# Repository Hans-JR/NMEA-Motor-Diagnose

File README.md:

# NMEA-Motor-Diagnose
Monitors several Boot Engine Parameter and converts them into the NMEA0183 protocoll

The Project is listet under the URL https://open-boat-projects.org/de/diy-motordiagnose/

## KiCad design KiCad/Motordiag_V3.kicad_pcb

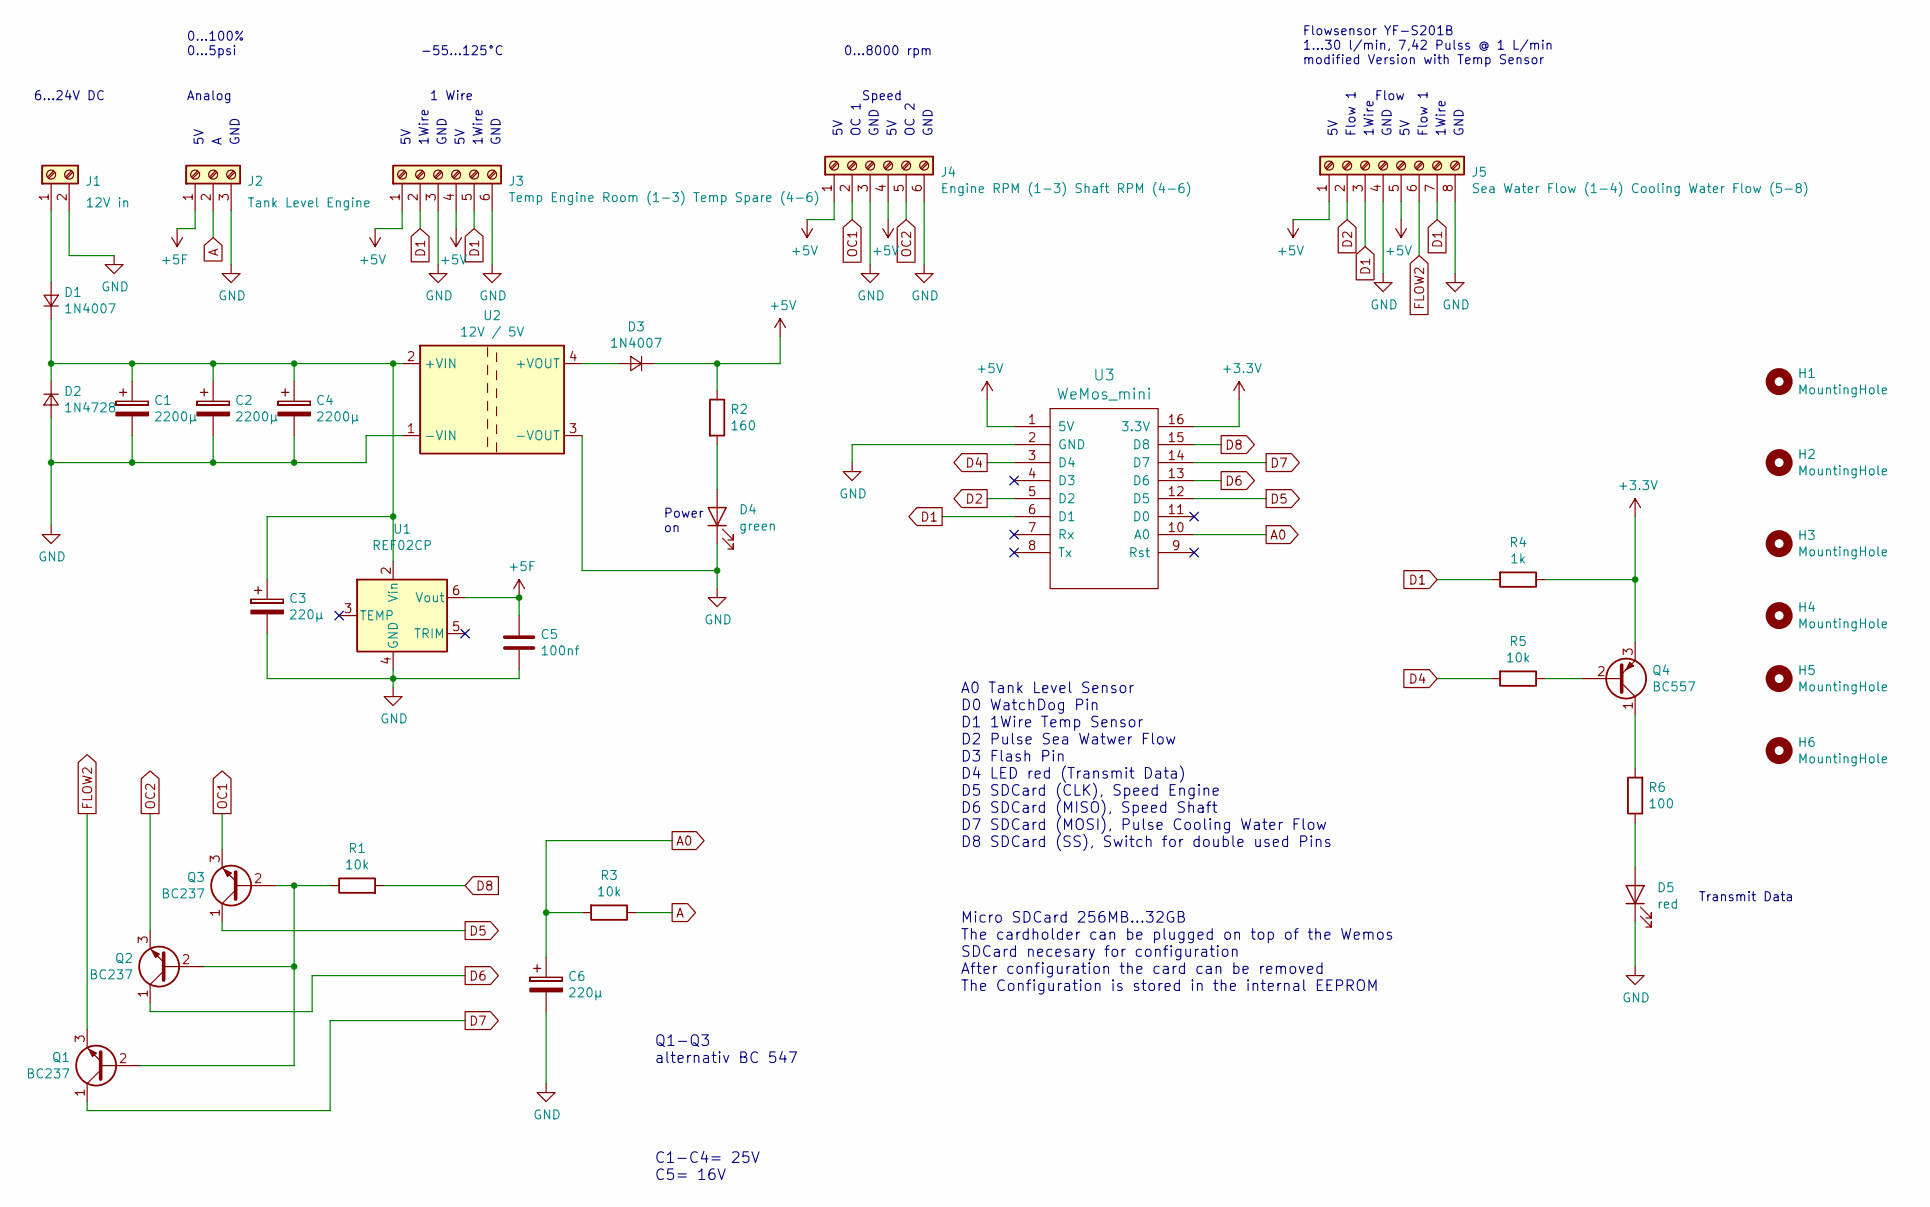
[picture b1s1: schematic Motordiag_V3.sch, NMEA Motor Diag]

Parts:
C1, C2, C4: 2200µ; CP_Radial_D12.5mm_P5.00mm
C3, C6: 220µ; CP_Radial_D8.0mm_P5.00mm
C5: 100nf; C_Rect_L7.0mm_W2.5mm_P5.00mm
D1, D3: 1N4007; D_DO-41_SOD81_P10.16mm_Horizontal
D2: 1N4728; D_DO-201_P12.70mm_Horizontal
D4: green; LED_D5.0mm
D5: red; LED_D5.0mm
H1, H2: MountingHole; MountingHole_3.2mm_M3
H3, H4, H5, H6: MountingHole; MountingHole_3.5mm_Pad
J1: 12V in; 250-202
J2: Tank Level Engine; 250-203
J3: Temp Engine Room (1-3) Temp Spare (4-6); 250-206
J4: Engine RPM (1-3) Shaft RPM (4-6); 250-206
J5: Sea Water Flow (1-4) Cooling Water Flow (5-8); 250-208
Q1, Q2, Q3: BC237; TO-92_Inline
Q4: BC557; TO-92_Inline
R1, R3, R5: 10k; R_Axial_DIN0309_L9.0mm_D3.2mm_P12.70mm_Horizontal
R2: 160; R_Axial_DIN0309_L9.0mm_D3.2mm_P12.70mm_Horizontal
R4: 1k; R_Axial_DIN0309_L9.0mm_D3.2mm_P12.70mm_Horizontal
R6: 100; R_Axial_DIN0309_L9.0mm_D3.2mm_P12.70mm_Horizontal
U1: REF02CP; DIP-8_W7.62mm
U2: 12V / 5V; Converter_DCDC_LM2596S_Modul
U3: WeMos_mini; D1_mini_board

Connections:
+3V3: Q4.3 (E), R4.1, U3.16 (3.3V)
+5F: C5.1, J2.1, U1.6 (Vout)
+5V: D3.1 (K), J3.1, J3.4, J4.1, J4.4, J5.1, J5.5, R2.1, U3.1 (5V)
A: J2.2, R3.1
A0: C6.1, R3.2, U3.10 (A0)
D1: J3.2, J3.5, J5.3, J5.7, R4.2, U3.6 (D1)
D2: J5.2, U3.5 (D2)
D4: R5.2, U3.3 (D4)
D5: Q3.1 (C), U3.12 (D5)
D6: Q2.1 (C), U3.13 (D6)
D7: Q1.1 (C), U3.14 (D7)
D8: R1.2, U3.15 (D8)
FLOW2: J5.6, Q1.3 (E)
GND: C1.2, C2.2, C3.2, C4.2, C5.2, C6.2, D2.2 (A), D4.1 (K), D5.1 (K), J1.2, J2.3, J3.3, J3.6, J4.3, J4.6, J5.4, J5.8, U1.4 (GND), U2.1 (-VIN), U2.3 (-VOUT), U3.2 (GND)
unnamed: C1.1, C2.1, C3.1, C4.1, D1.1 (K), D2.1 (K), U1.2 (Vin), U2.2 (+VIN)
unnamed: D1.2 (A), J1.1
unnamed: D3.2 (A), U2.4 (+VOUT)
unnamed: D4.2 (A), R2.2
unnamed: D5.2 (A), R6.1
unnamed: Q1.2 (B), Q2.2 (B), Q3.2 (B), R1.1
unnamed: Q4.1 (C), R6.2
unnamed: Q4.2 (B), R5.1
OC1: J4.2, Q3.3 (E)
OC2: J4.5, Q2.3 (E)

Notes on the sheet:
GND
1Wire
Analog
1 Wire
Speed
OC 1
OC 2
Flow
Flow 1
C1-C4= 25V C5= 16V
6...24V DC
0...100% 0...5psi
-55...125°C
0...8000 rpm
Flowsensor YF-S201B 1...30 l/min, 7,42 Pulss @ 1 L/min modified Version with Temp Sensor
Transmit Data
Power on
Micro SDCard 256MB...32GB The cardholder can be plugged on top of the Wemos SDCard necesary for configuration After configuration the card can be removed The Configuration is stored in the internal EEPROM
A0 Tank Level Sensor D0 WatchDog Pin D1 1Wire Temp Sensor D2 Pulse Sea Watwer Flow D3 Flash Pin D4 LED red (Transmit Data) D5 SDCard (CLK), Speed Engine D6 SDCard (MISO), Speed Shaft D7 SDCard (MOSI), Pulse Cooling Water Flow D8 SDCard (SS), Switch for double used Pins
Q1-Q3 alternativ BC 547

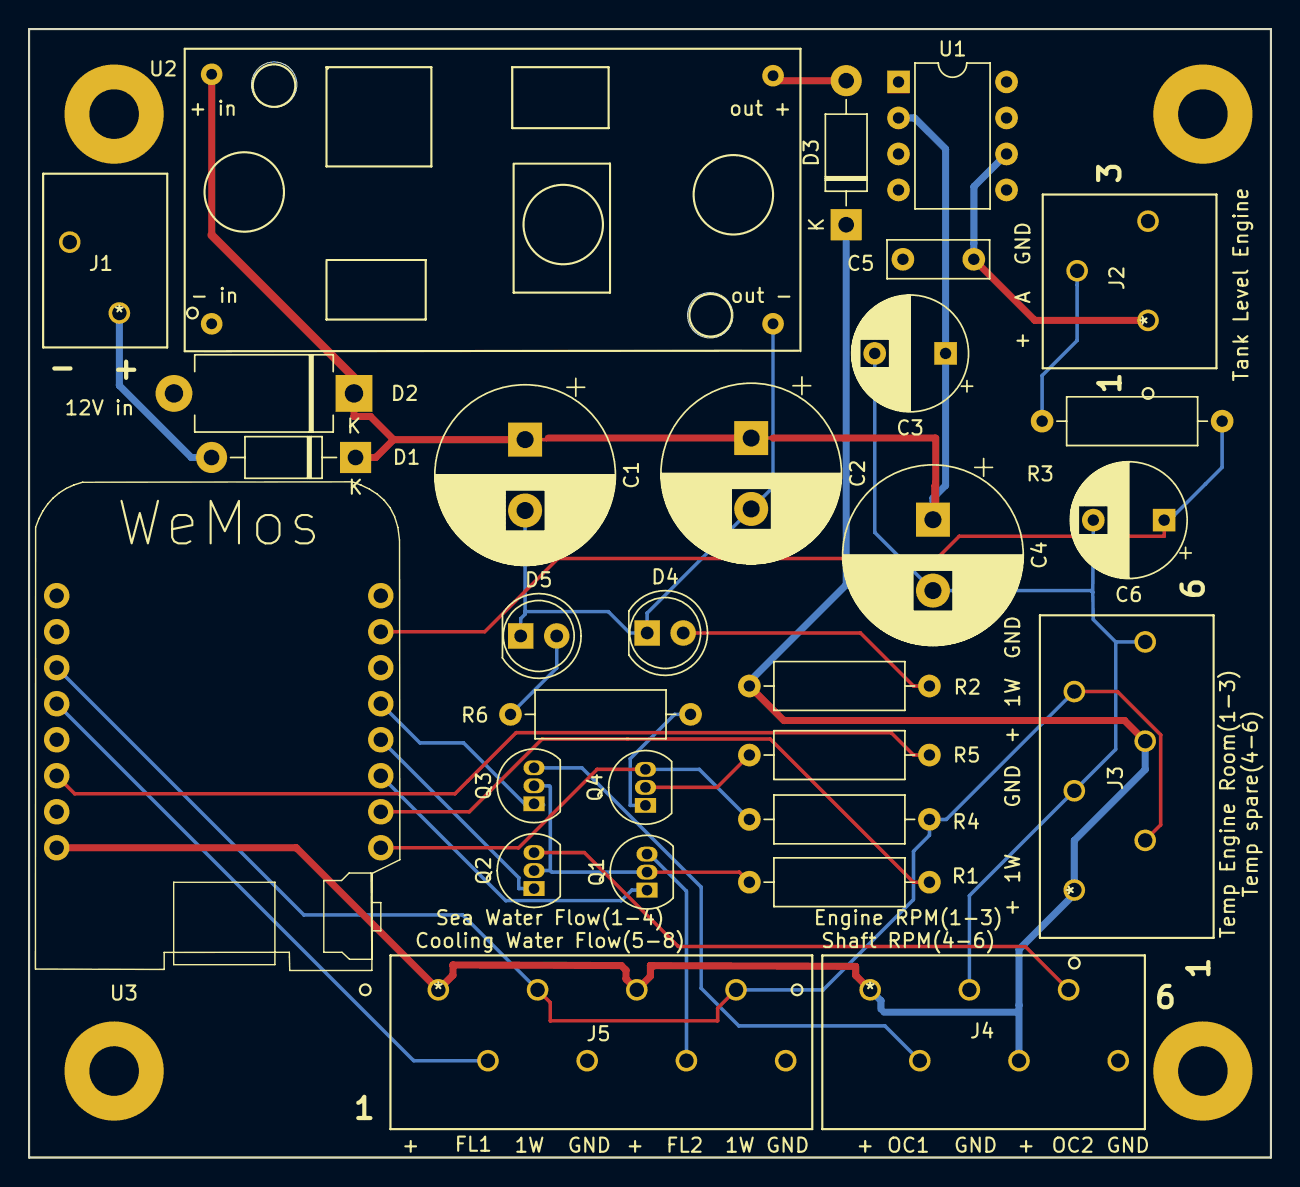
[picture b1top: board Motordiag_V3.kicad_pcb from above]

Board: 2 copper layers, 87.6 x 79.6 mm, 35 parts (0 on the bottom side), 24 nets.

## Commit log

2021-12-27 Create KiCad
2021-12-27 Create Files

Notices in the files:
KiCad/Motordiag_V3.kicad_pcb:
CC BY-NC-SA
parts and their libraries:
Copyright 2016 Accelerated Designs. All rights reserved.
